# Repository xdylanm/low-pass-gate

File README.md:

# Low Pass Gate

Buchla-style VCA and Sallen-Key VCF with vactrols.

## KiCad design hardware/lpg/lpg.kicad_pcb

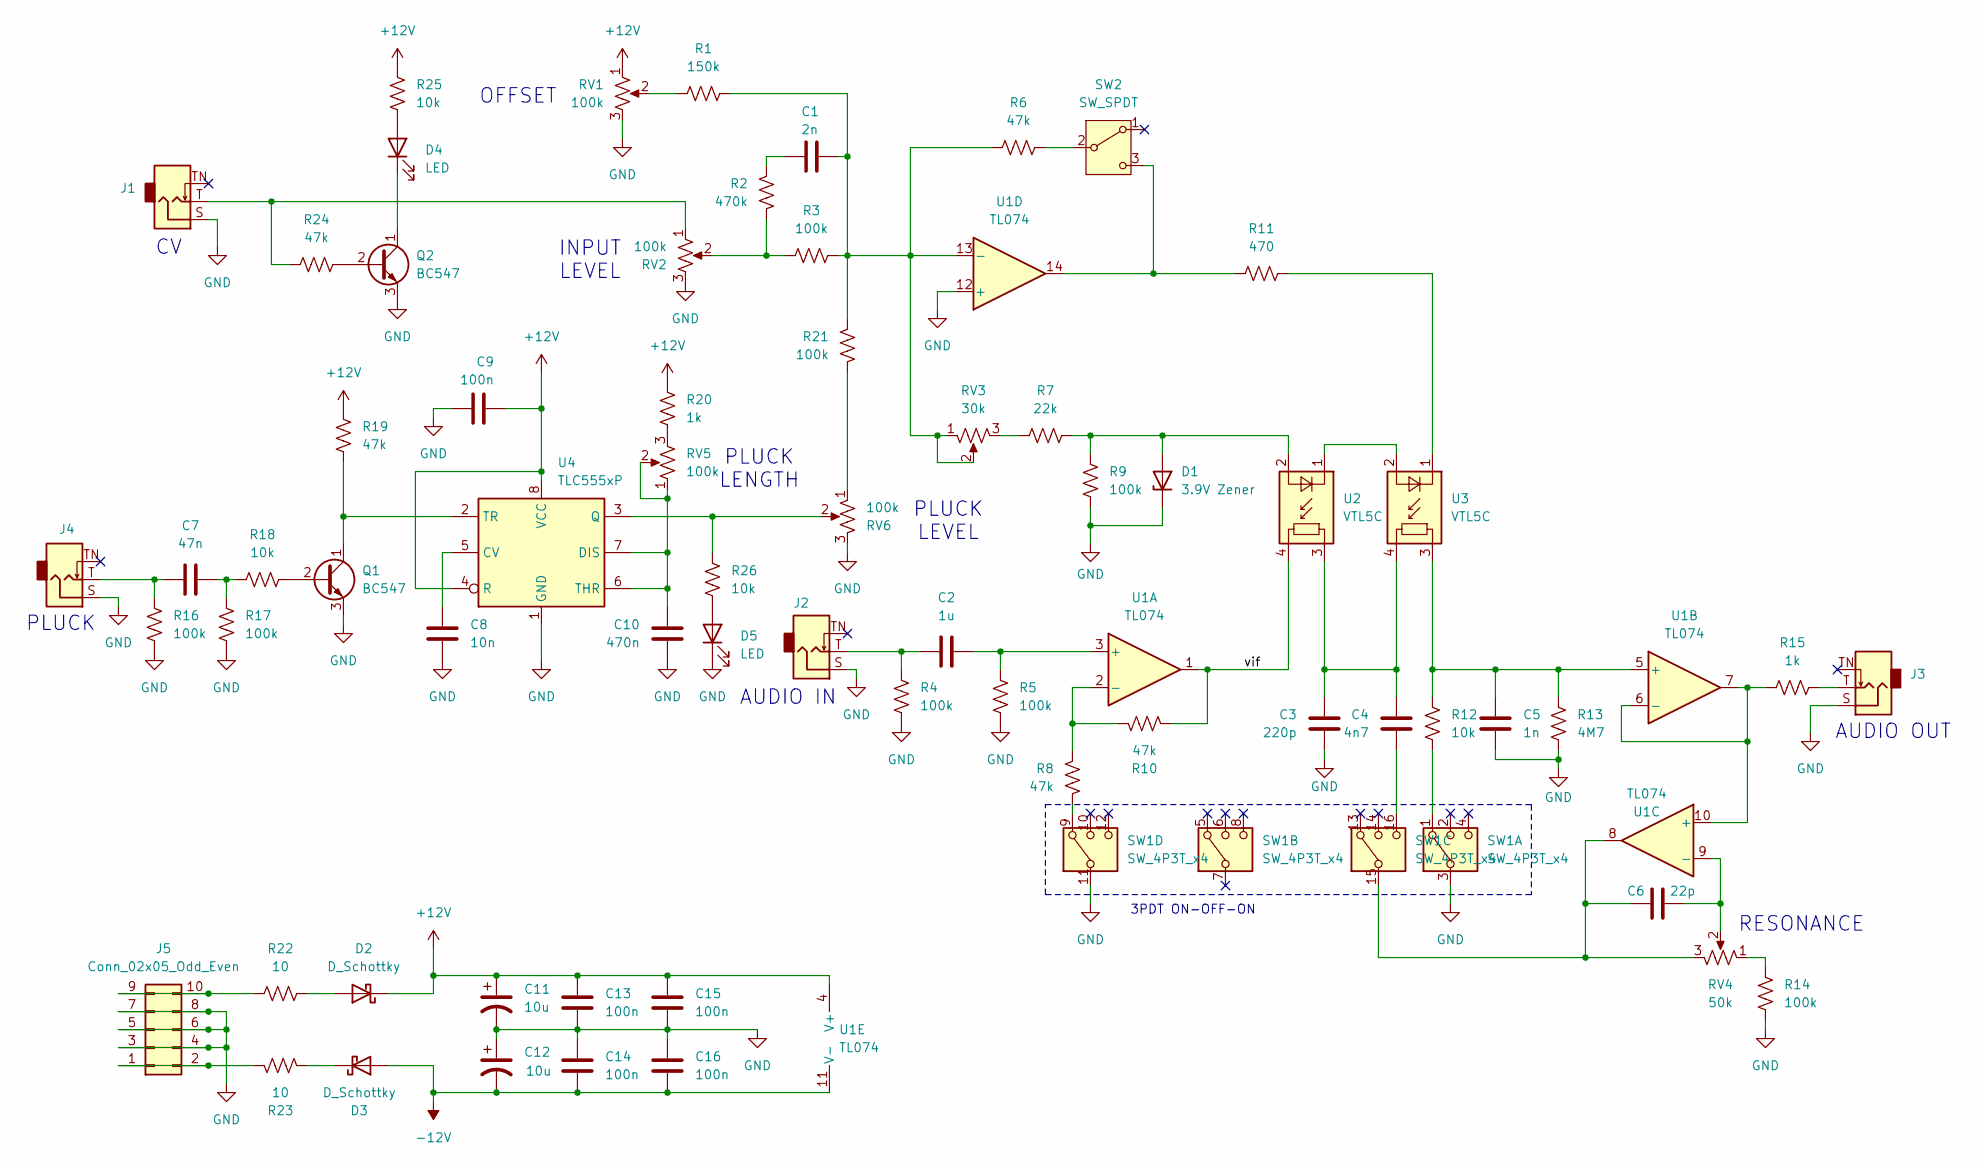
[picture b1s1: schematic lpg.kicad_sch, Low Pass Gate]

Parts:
C1: 2n; C_Disc_D5.0mm_W2.5mm_P2.50mm
C2: 1u; C_Disc_D5.0mm_W2.5mm_P2.50mm
C3: 220p; C_Disc_D5.0mm_W2.5mm_P2.50mm
C4: 4n7; C_Disc_D5.0mm_W2.5mm_P2.50mm
C5: 1n; C_Disc_D5.0mm_W2.5mm_P5.00mm
C6: 22p; C_Disc_D5.0mm_W2.5mm_P2.50mm
C7: 47n; C_Disc_D5.0mm_W2.5mm_P2.50mm
C8: 10n; C_Disc_D5.0mm_W2.5mm_P2.50mm
C9, C13, C14, C16: 100n; C_Disc_D5.0mm_W2.5mm_P2.50mm
C10: 470n; C_Disc_D5.0mm_W2.5mm_P2.50mm
C11, C12: 10u; CP_Radial_D5.0mm_P2.00mm
C15: 100n; C_Disc_D5.0mm_W2.5mm_P5.00mm
D1: 3.9V Zener; D_DO-35_SOD27_P2.54mm_Vertical_AnodeUp
D2, D3: D_Schottky; D_DO-41_SOD81_P2.54mm_Vertical_AnodeUp
D4, D5: LED; LED_D3.0mm
J1, J2, J3, J4: AudioJack2_SwitchT; Jack_3.5mm_QingPu_WQP-PJ301M-12_Vertical
J5: Conn_02x05_Odd_Even; IDC-Header_2x05_P2.54mm_Vertical
Q1, Q2: BC547; TO-92_Inline_Wide
R1: 150k; R_Axial_DIN0204_L3.6mm_D1.6mm_P2.54mm_Vertical
R2: 470k; R_Axial_DIN0204_L3.6mm_D1.6mm_P2.54mm_Vertical
R3, R4, R5, R9, R14, R16, R17, R21: 100k; R_Axial_DIN0204_L3.6mm_D1.6mm_P2.54mm_Vertical
R6, R8, R10, R19, R24: 47k; R_Axial_DIN0204_L3.6mm_D1.6mm_P2.54mm_Vertical
R7: 22k; R_Axial_DIN0204_L3.6mm_D1.6mm_P2.54mm_Vertical
R11: 470; R_Axial_DIN0207_L6.3mm_D2.5mm_P10.16mm_Horizontal
R12, R25: 10k; R_Axial_DIN0207_L6.3mm_D2.5mm_P15.24mm_Horizontal
R13: 4M7; R_Axial_DIN0204_L3.6mm_D1.6mm_P2.54mm_Vertical
R15, R20: 1k; R_Axial_DIN0204_L3.6mm_D1.6mm_P2.54mm_Vertical
R18, R26: 10k; R_Axial_DIN0204_L3.6mm_D1.6mm_P2.54mm_Vertical
R22, R23: 10; R_Axial_DIN0207_L6.3mm_D2.5mm_P2.54mm_Vertical
RV1, RV2, RV5, RV6: 100k; Potentiometer_Bourns_PTV09A-1_Single_Vertical
RV3: 30k; Potentiometer_Piher_PT-6-V_Vertical
RV4: 50k; Potentiometer_Bourns_PTV09A-1_Single_Vertical
SW1: SW_4P3T_x4; SW_4P3T_SS-43D01_NoFrame
SW2: SW_SPDT; SW_Dailywell_SPDT_2MS1T1B1M1
U1: TL074; DIP-14_W7.62mm_Socket
U2, U3: VTL5C; PerkinElmer_VTL5C
U4: TLC555xP; DIP-8_W7.62mm_Socket

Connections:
+12V: C9.1, C11.1, C13.2, C15.2, D2.1 (K), R19.1, R20.1, R25.2, RV1.1, U1.4 (V+), U4.4 (R), U4.8 (VCC)
-12V: C12.2, C14.1, C16.1, D3.2 (A), U1.11 (V-)
/vif: R10.2, U1.1, U2.4
GND: C3.1, C5.1, C8.1, C9.2, C10.1, C11.2, C12.1, C13.1, C14.2, C15.1, C16.2, D1.1 (K), D5.1 (K), J1.S, J2.S, J3.S, J4.S, J5.3, J5.4, J5.5, J5.6, J5.7, J5.8, Q1.3 (E), Q2.3 (E), R4.1, R5.1, R9.2, R13.2, R14.2, R16.1, R17.1, RV1.3, RV2.3, RV6.3, SW1.3, SW1.11, U1.12 (+), U4.1 (GND)
unnamed: C1.1, R2.1
unnamed: C2.1, J2.T, R4.2
unnamed: C3.2, C4.2, U2.3, U3.4
unnamed: C4.1, SW1.16
unnamed: C6.2, RV4.3, SW1.15, U1.8
unnamed: C7.1, J4.T, R16.2
unnamed: C7.2, R17.2, R18.2
unnamed: D1.2 (A), R7.1, R9.1, U2.2 (+)
unnamed: D2.2 (A), R22.1
unnamed: D3.1 (K), R23.1
unnamed: D4.2 (A), R25.1
unnamed: D4.1 (K), Q2.1 (C)
unnamed: D5.2 (A), R26.1
unnamed: J1.T, R24.1, RV2.1
unnamed: J3.T, R15.2
unnamed: J5.1, J5.2, R23.2
unnamed: J5.9, J5.10, R22.2
unnamed: Q1.2 (B), R18.1
unnamed: Q1.1 (C), R19.2, U4.2 (TR)
unnamed: Q2.2 (B), R24.2
unnamed: R1.2, RV1.2
unnamed: R2.2, R3.2, RV2.2
unnamed: R7.2, RV3.3
unnamed: R8.2, SW1.9
unnamed: R12.2, SW1.1
unnamed: R14.1, RV4.1
unnamed: R20.2, RV5.3
unnamed: R21.2, RV6.1
unnamed: R6.1, SW2.2 (B)
unnamed: R11.2, SW2.3 (C), U1.14
unnamed: C2.2, R5.2, U1.3 (+)
unnamed: R8.1, R10.1, U1.2 (-)
unnamed: C5.2, R12.1, R13.1, U1.5 (+), U3.3
unnamed: R15.1, U1.6 (-), U1.7, U1.10 (+)
unnamed: C6.1, RV4.2, U1.9 (-)
unnamed: C1.2, R1.1, R3.1, R6.2, R21.1, RV3.1, RV3.2, U1.13 (-)
unnamed: U2.1 (-), U3.2 (+)
unnamed: R11.1, U3.1 (-)
unnamed: C8.2, U4.5 (CV)
unnamed: C10.2, RV5.1, RV5.2, U4.6 (THR), U4.7 (DIS)
unnamed: R26.2, RV6.2, U4.3 (Q)

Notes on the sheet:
RESONANCE
INPUT LEVEL
AUDIO IN
3PDT ON-OFF-ON
PLUCK
PLUCK LEVEL
AUDIO OUT
PLUCK LENGTH
OFFSET

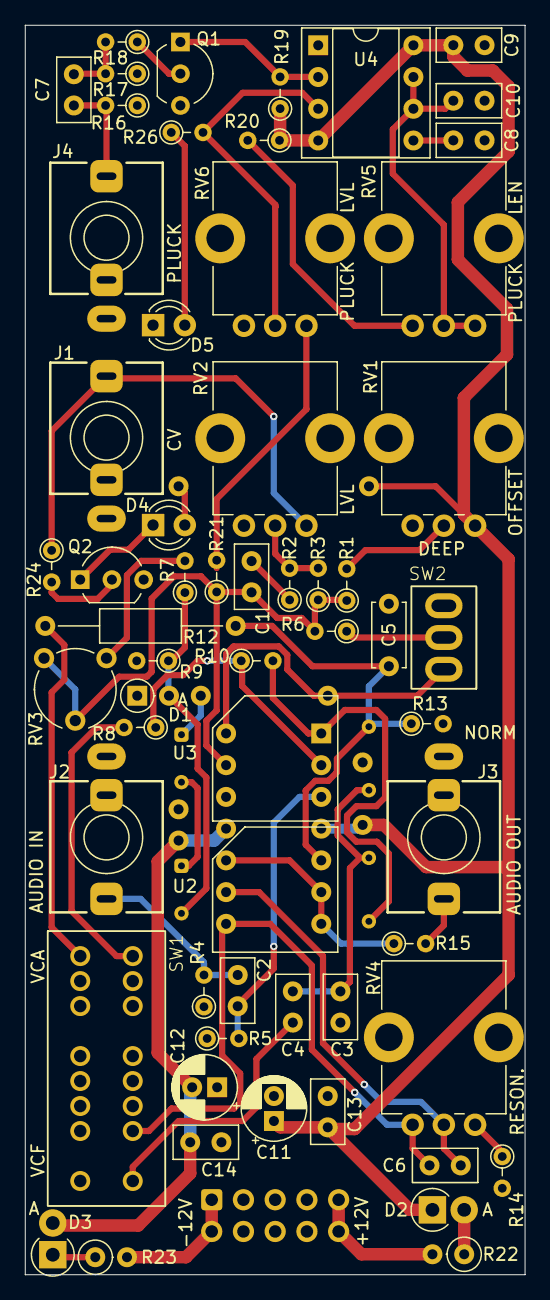
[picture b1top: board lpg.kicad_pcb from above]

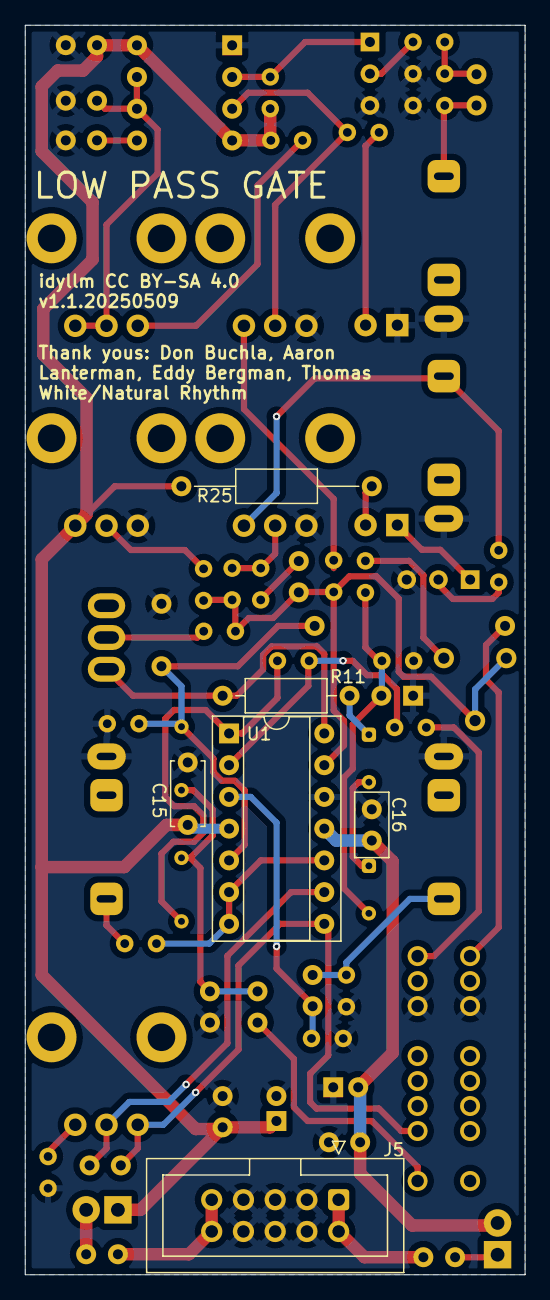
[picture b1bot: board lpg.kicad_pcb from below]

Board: 2 copper layers, 40.0 x 100.0 mm, 66 parts (6 on the bottom side), 45 nets.

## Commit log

2024-10-03 Initial version of circuit and PCB for fabrication
2024-10-03 updated theory doc
2024-10-03 removed wrong image
2024-10-03 adding readthedocs config
2024-10-03 fixing readthedocs config
2024-10-03 adding requirements.txt for myst_parser for RTD
2024-10-03 adding math parsing support
2024-10-03 adding math parsing support 2
2024-10-03 more math fixes, style change
2024-10-03 more styling fixes
2024-10-03 spacing in theory.md for math
2025-03-10 replaced switches with 4P3T slider and SPDT M5 sub-mini toggle
2025-03-10 boards for v1.1
2025-04-30 Faceplate layout and silkscreen
2026-05-26 Update KiCad project settings and error handling parameters
    - Added new error handling for "creepage", "hole_to_hole", "text_on_edge_cuts", "track_angle", and "track_segment_length".
    - Set "footprint_filters_mismatch" and "footprint_type_mismatch" to "ignore".
    - Updated teardrop options to include "td_onpthpad" and "td_onsmdpad".
    - Introduced "min_groove_width" parameter.
    - Adjusted version numbers in meta information.
    - Added "priority" field to net settings.
2026-05-26 Add documentation for Low Pass Gate module and remove legacy files
    - Created index.md for module overview and features.
    - Removed make.bat and assembly.md as part of documentation cleanup.
    - Added arithmatex-config.js for MathJax configuration.
    - Deleted conf.py, index.rst, and requirements.txt to streamline documentation setup.
    - Introduced extra.css for custom styles and improved visual elements.
    - Added theory.md detailing the design and functionality of the Sallen-Key filter and Buchla 292 style low-pass gate.

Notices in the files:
hardware/lpg/lpg.kicad_pcb:
idyllm CC BY-SA 4.0
hardware/lpg/lpg.kicad_sch:
CC BY-SA 4.0
